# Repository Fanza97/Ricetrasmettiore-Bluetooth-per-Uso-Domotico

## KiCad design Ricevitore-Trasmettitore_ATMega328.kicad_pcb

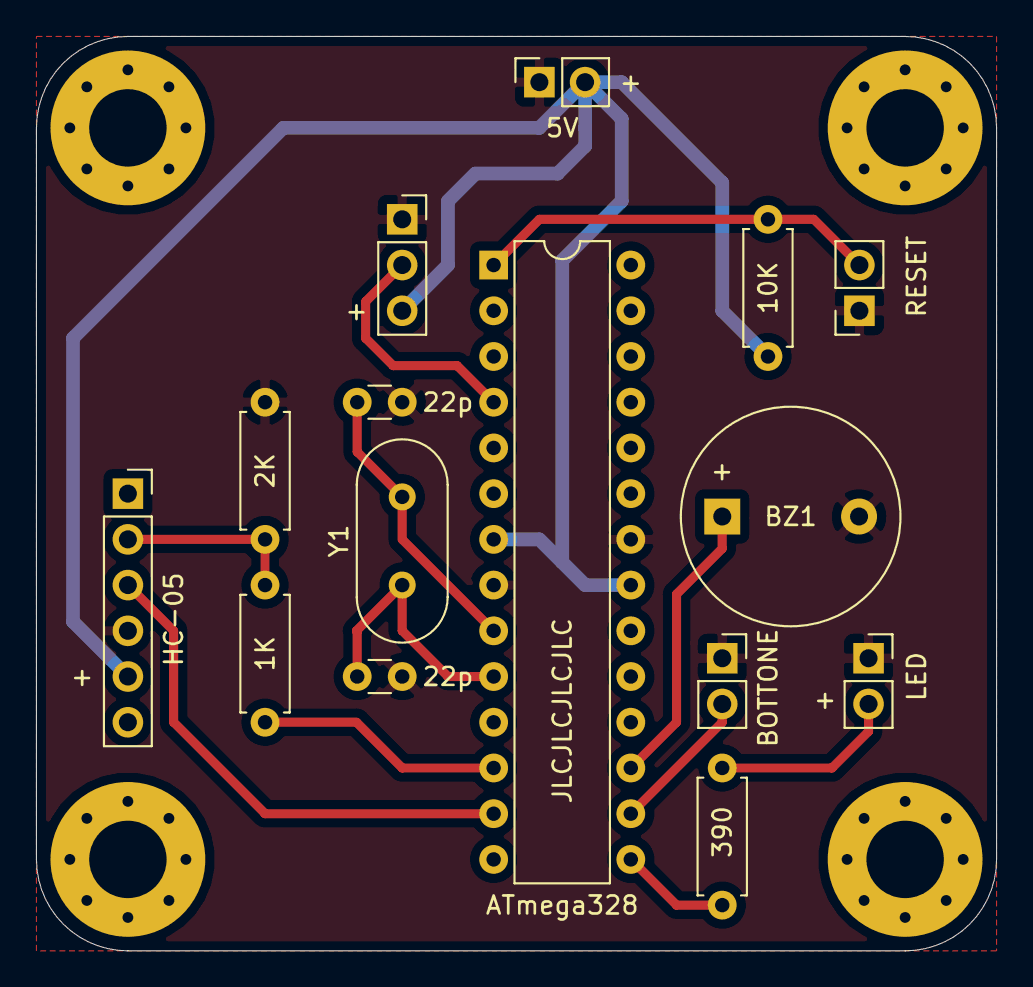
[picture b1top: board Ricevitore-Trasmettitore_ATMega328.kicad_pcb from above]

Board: 2 copper layers, 53.3 x 50.8 mm, 19 parts (0 on the bottom side), 13 nets.

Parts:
1K: 1k; R_Axial_DIN0207_L6.3mm_D2.5mm_P7.62mm_Horizontal
2K: 2k; R_Axial_DIN0207_L6.3mm_D2.5mm_P7.62mm_Horizontal
5V : Conn_01x02; PinSocket_1x02_P2.54mm_Vertical
10K: 10k; R_Axial_DIN0207_L6.3mm_D2.5mm_P7.62mm_Horizontal
22p, 22p#2: 22p; C_Disc_D3.0mm_W1.6mm_P2.50mm
390: 390; R_Axial_DIN0207_L6.3mm_D2.5mm_P7.62mm_Horizontal
+: Conn_01x02; PinSocket_1x02_P2.54mm_Vertical
+#2: Conn_01x03; PinSocket_1x03_P2.54mm_Vertical
+#3: Conn_01x06; PinSocket_1x06_P2.54mm_Vertical
ATmega328: ATmega328-PU; DIP-28_W7.62mm
BOTTONE: Conn_01x02; PinSocket_1x02_P2.54mm_Vertical
BZ1: Buzzer; Buzzer_12x9.5RM7.6
H1, H2, H3, H4: MountingHole; MountingHole_4.3mm_M4_Pad_Via
RESET: Conn_01x02; PinSocket_1x02_P2.54mm_Vertical
Y1: Crystal; Crystal_HC18-U_Vertical

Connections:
BOTTONE: ATmega328.16, BOTTONE.2
BUZZER: ATmega328.17, BZ1.1
GND: 2K.2, 5V.1, 22p.1, 22p#2.1, +.1, +#2.1, +#3.4, ATmega328.8, ATmega328.22, BOTTONE.1, BZ1.2, RESET.1
INTERRUPT: +#2.2, ATmega328.4
LED: 390.1, ATmega328.15
unnamed: 22p.2, ATmega328.9, Y1.2
unnamed: 22p#2.2, ATmega328.10, Y1.1
unnamed: 390.2, +.2
PARTITORE: 1K.2, 2K.1, +#3.2
RESET: 10K.2, ATmega328.1, RESET.2
RX: +#3.3, ATmega328.13
TX: 1K.1, ATmega328.12
VCC: 5V.2, 10K.1, +#2.3, +#3.5, ATmega328.7, ATmega328.20, ATmega328.21
